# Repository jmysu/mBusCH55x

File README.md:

# mBusCH55x
An affordable USB-CDC dev board, **CH552E/CH554G/CH559T** compatible!<br>
 
 <br>

As of 0801-2024, the list price on LCSC site: <br>
 <br>

<br>

>Firmware supported: <br>
   cdcCMDs (CH55x) <br>
 <br>
   TinyBasic cdc559-1000 (CH559) <br>
 <br>
 
<br><br><br><br><br><br><br><br><br><br><br><br><br><br><br><br><br><br>
<br>

What's inside: <br>
left:CH55x right:CH559 <br>
<br>
<br>
<br><br><br><br><br><br><br><br><br><br><br><br><br><br><br><br><br><br>

<br>

---
[Related WiKi](https://github.com/jmysu/mBusSTM32CH55x/wiki) Related WiKi w/ STM32 <br>
<br>

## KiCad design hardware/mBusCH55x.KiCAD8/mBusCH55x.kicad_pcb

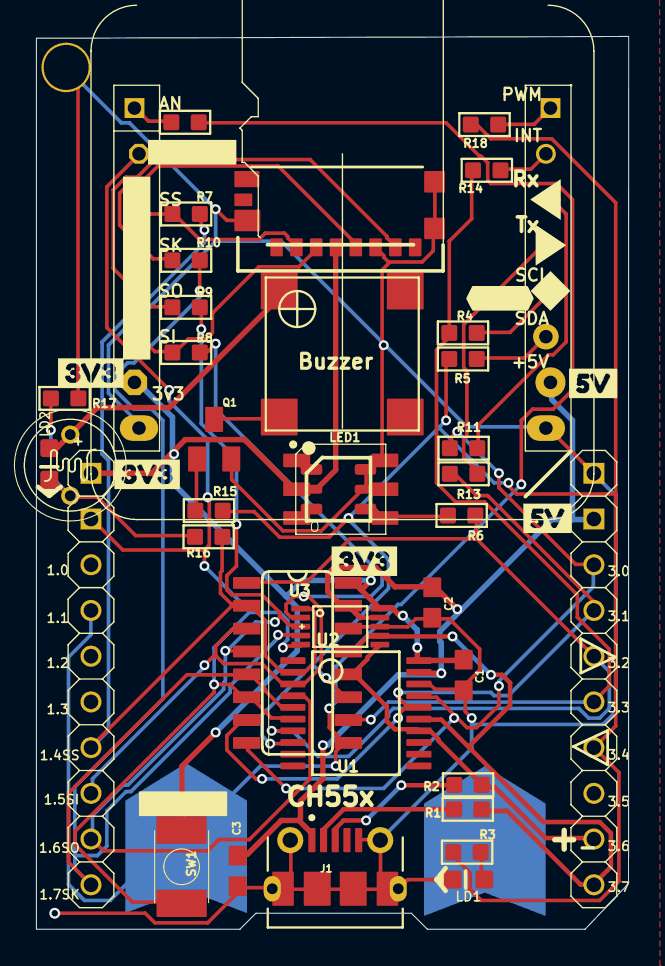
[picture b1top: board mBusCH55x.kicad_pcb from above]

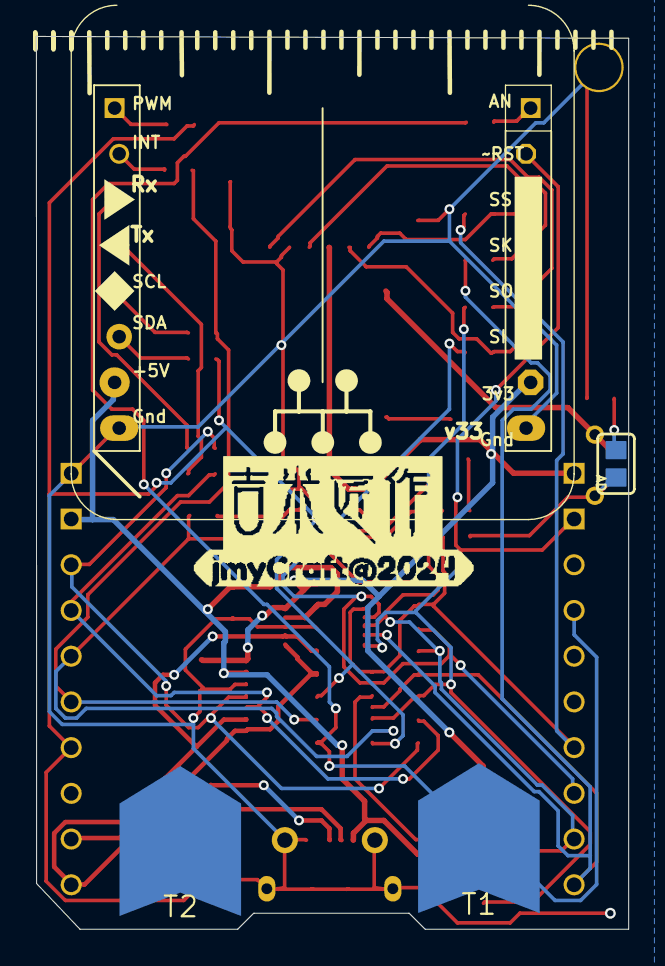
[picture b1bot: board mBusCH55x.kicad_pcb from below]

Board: 2 copper layers, 32.9 x 49.6 mm, 50 parts (4 on the bottom side), 38 nets.

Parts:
$1_10_$_2024-07-29_05-42-51: JMYCRAFT#20240; JMYCRAFT#20240_43069666
BZ1: MBUSSTM32_BUZZER; MBUSSTM32_SMT-8585-BUZZER
C1, C2: 0.1uF; MBUSUSB55X_C0603
C3: 1uF; MBUSUSB55X_C0603
H1: 2.75/2.52.75/2.5; 2.75_2.5_43069666
J1: microUSB; MBUSUSB55X_MOLEX_1050170001
J2: MBUSPICOWROOM_TF0475710001; MBUSPICOWROOM_MOLEX_0475710001
JP1, JP2: 1X10
LB1, LB3: 3V30; 3V30_43170660
LB2, LB5: #RESET#2052; #RESET#2052_37869809
LB4: #I2C#2047; #I2C#2047_43069666
LB12: MBUSPICO_3V30
LD1: GREEN; MBUSUSB55X_LED-0603
LD2: GREEN; MBUSSTM32_LED-0603
LED1: WS2813_3535; MBUSSTM32_PICOMATE_WS2813-50503535
LOGO1: JIMMYCRAFT
MB1: MBUSSTM32_MIKROBUS
PH1: DNP/A1050_09/5mmLED; MBUSSTM32_T0-46-A10XX
Q1: MBUSSTM32_BSS123; MBUSSTM32_SOT23
R1, R2: 33 Ohm; MBUSUSB55X_R0603
R3, R12, R14: 1K; MBUSUSB55X_R0603
R4, R5: 33; MBUSUSB55X_R0603
R6, R7, R8, R9, R10, R11, R13, R18: 330; MBUSUSB55X_R0603
R15: 330Ohm; MBUSSTM32_R0603
R16: 1K; MBUSSTM32_R0603
R17: 10K; MBUSSTM32_R0603
SJ1: DNP; MBUSSTM32_SJ
SW1: TACT4X3; MBUSUSB55X_PICOMATE_SPST4X3
T1, T2: DVPGDI_CAP_SENSE
U1: CH559T (SSOP20); SSOP20
U2: CH552E; MSOP10
U3: CH552G; MBUSUSB55X_MY_IC_SO16
U$1, U$4: 5V0

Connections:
#4VO: BZ1.+, LD2.A, PH1.1
#D+: J1.3, R2.1
#D-: J1.2, R1.1
#DO: LED1.3, LED1.9
AD2: LD2.C, PH1.2, R16.1, SJ1.1
AN: MB1.1, R12.1
GND: C1.2, C2.2, C3.2, H1.1, J1.5, J1.SH1, J1.SH2, J1.SH3, J1.SH4, J1.SH5, J1.SH6, J1.SH7, J1.SH8, J2.6, J2.9, J2.10, J2.13, JP1.1, LD1.C, LED1.5, LED1.6, LED1.11, LED1.12, MB1.8, MB1.9, Q1.2, R17.2, U1.18, U2.8, U3.14
INT: MB1.15, R14.1
LED: LD1.A, R3.1
MISO: J2.7, MB1.5, R9.2
MOSI: J2.3, MB1.6, R8.2
unnamed: BZ1.-, Q1.3
unnamed: Q1.1, R15.1
unnamed: R17.1, SJ1.2
unnamed: LED1.1, LED1.7
NEO_DI: LED1.4, LED1.10, R6.2
P1.1/A0/T1: JP2.4, R12.2, T1.2, U3.9
P1.4/A1/SS: JP2.7, R7.1, R16.2, U1.2, U2.1, U3.2
P1.5/MOSI/T3: JP2.8, R8.1, U1.3, U2.2, U3.3
P1.6/MISO: JP2.9, R9.1, U1.4, U2.3, U3.4
P1.7/SCK: JP2.10, R10.1, U1.5, U2.4, U3.5
P3.0/PWM0/RX: JP1.3, R11.1, U1.17, U3.8
P3.1/PWM1/TX: JP1.4, R13.1, U1.16, U3.7
P3.2/A3/TXD1: JP1.5, R6.1, U1.7, U3.1
P3.3/INT1: JP1.6, R4.2, R14.2, U3.10
P3.4/RXD1/PWM2: JP1.7, R3.2, R5.2, R15.2, R18.1, U1.8, U3.11
P3.6/USB_D+: JP1.9, R2.2, U1.14, U2.6, U3.12
P3.7/USB_D-: JP1.10, R1.2, U1.15, U2.7, U3.13
PWM: MB1.16, R18.2
RST: JP2.2, MB1.2, SW1.P$1, U1.6, U2.5, U3.6
RX: MB1.14, R11.2
SCL: MB1.12, R4.1
SDA: MB1.11, R5.1
SK: J2.5, MB1.4, R10.2
SS: J2.2, MB1.3, R7.2
TX: MB1.13, R13.2
USB5V: C2.1, C3.1, J1.1, JP1.2, MB1.10, U1.19, U2.9, U3.15
V33: C1.1, J2.4, JP2.1, LED1.2, LED1.8, MB1.7, SW1.P$2, U1.20, U2.10, U3.16

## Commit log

2024-08-16 Add neopixel cmd
    Add neo.h neo.c
